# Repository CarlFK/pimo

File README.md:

Pico for pmod hatish.

https://kicanvas.org/?github=https%3A%2F%2Fgithub.com%2FCarlFK%2Fpimo%2Ftree%2Fmain%2Fproject

A hat to hold a pico in place so it isn't flopping around.
4 pins to a header to ribbon cable to the arty pmod.

Sligthly better than bread board and double sided tape
￼
copied pj, so there is a bunch of jtag and spi flash stuff left over.

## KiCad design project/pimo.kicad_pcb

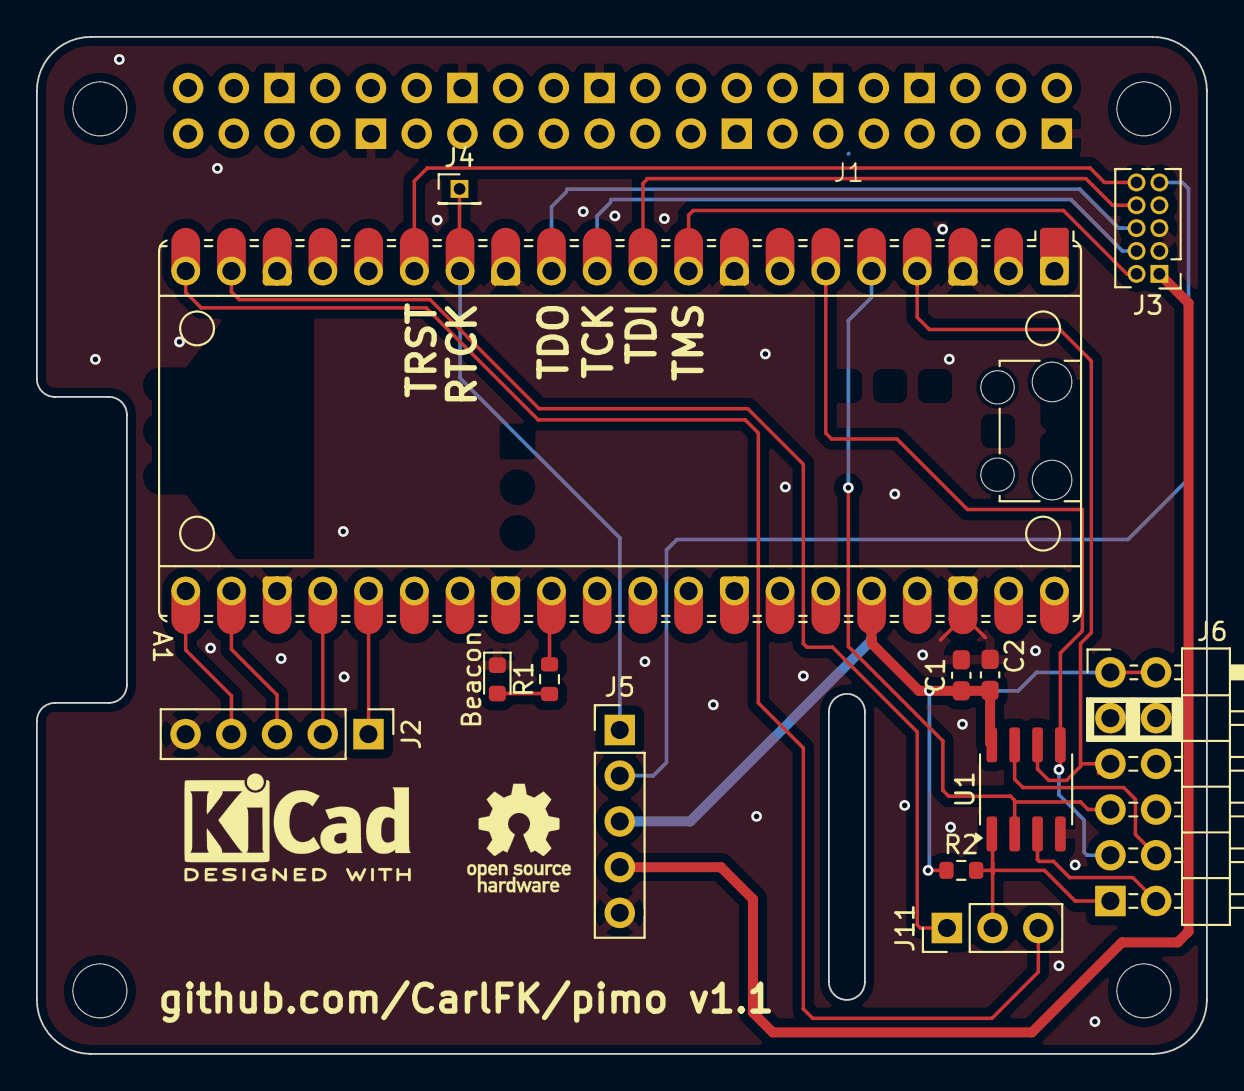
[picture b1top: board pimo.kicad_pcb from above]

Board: 2 copper layers, 65.0 x 56.5 mm, 14 parts (0 on the bottom side), 24 nets.

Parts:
A1: RaspberryPi_Pico; RaspberryPi_Pico_Common
C1: .1; C_0603_1608Metric_Pad1.08x0.95mm_HandSolder
C2: 1; C_0603_1608Metric_Pad1.08x0.95mm_HandSolder
D1: Beacon; LED_0603_1608Metric
J1: RPi_GPIO; RPI_Hat_B+
J2, J5: Conn_01x05_Pin; PinHeader_1x05_P2.54mm_Vertical
J3: Conn_ARM_JTAG_SWD_10; PinHeader_2x05_P1.27mm_Vertical
J4: Conn_01x01; PinHeader_1x01_P1.27mm_Vertical
J6: 2.54-2*6P Bend insert; PinHeader_2x06_P2.54mm_PMODPeriph2B
J11: Conn_01x03_Pin; PinHeader_1x03_P2.54mm_Vertical
R1: 4.7k; R_0603_1608Metric
R2: 1k; R_0603_1608Metric
U1: W25Q32JVSS; SOIC-8_3.9x4.9mm_P1.27mm

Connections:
+3.3V: A1.36 (3V3), C1.1, C2.1, J5.3, J6.6 (VCC), J6.12 (VCC), R2.1, U1.8 (VCC)
/GNDDetect: J3.9 (GNDDetect), J5.2
/NC/TDI: A1.10 (GPIO7), J3.8 (NC/TDI)
/RPI_SPI_CE0: A1.19 (GPIO14), J11.1
/RPI_SPI_CE1: A1.20 (GPIO15), J11.3
/RTCK: A1.14 (GPIO10), J4.1, J5.1
/SWCLK/TCK: A1.11 (GPIO8), J3.4 (SWCLK/TCK)
/SWDIO/TMS: A1.9 (GPIO6), J3.2 (SWDIO/TMS)
/SWO/TDO: A1.12 (GPIO9), J3.6 (SWO/TDO)
/VTref: J3.1 (VTref), J5.4
/~RESET: A1.15 (GPIO11), J3.10 (~RESET)
GND: A1.3 (GND), A1.8 (GND), A1.13 (GND), A1.18 (GND), A1.23 (GND), A1.28 (GND), A1.38 (GND), C1.2, C2.2, D1.1 (K), J1.6 (GND), J1.9 (GND), J1.14 (GND), J1.20 (GND), J1.25 (GND), J1.30 (GND), J1.34 (GND), J1.39 (GND), J2.5, J3.3 (GND), J3.5 (GND), J5.5, J6.5 (GND), J6.11 (GND), U1.4 (GND)
unnamed: A1.21 (GPIO16), J2.4
unnamed: A1.22 (GPIO17), J2.3
unnamed: A1.24 (GPIO18), J2.2
unnamed: A1.25 (GPIO19), J2.1
unnamed: A1.29 (GPIO22), R1.2
unnamed: D1.2 (A), R1.1
PMOD1_IN: J6.1 (IO1), J11.2, R2.2, U1.1 (~CS)
PMOD2: A1.6 (GPIO4), J6.2 (IO2), U1.5 (DI(IO0))
PMOD3: A1.5 (GPIO3), J6.3 (IO3), U1.2 (DO(IO1))
PMOD4: A1.4 (GPIO2), J6.4 (IO4), U1.6 (CLK)
PMOD5: J6.7 (IO5), U1.3 (IO2)
PMOD6: J6.8 (IO6), U1.7 (IO3)

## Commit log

2025-03-30 copy pj, scrub unneededs
2025-03-30 pmod added.
2025-03-30 jtag symbol added
2025-03-31 touched by kicad v9.
2025-03-31 removed unused traces. and some used ones.
2025-03-31 removed more unused traces. and some used ones.
2025-03-31 added back spi flasg CS trace.
2025-03-31 added most of the things.
2025-03-31 smaller spi footprint
2025-03-31 KiCanvas url in readme.
2025-04-01 bonus jtag header
2025-04-01 label v1.0
2025-04-02 pmod header. v1.1
